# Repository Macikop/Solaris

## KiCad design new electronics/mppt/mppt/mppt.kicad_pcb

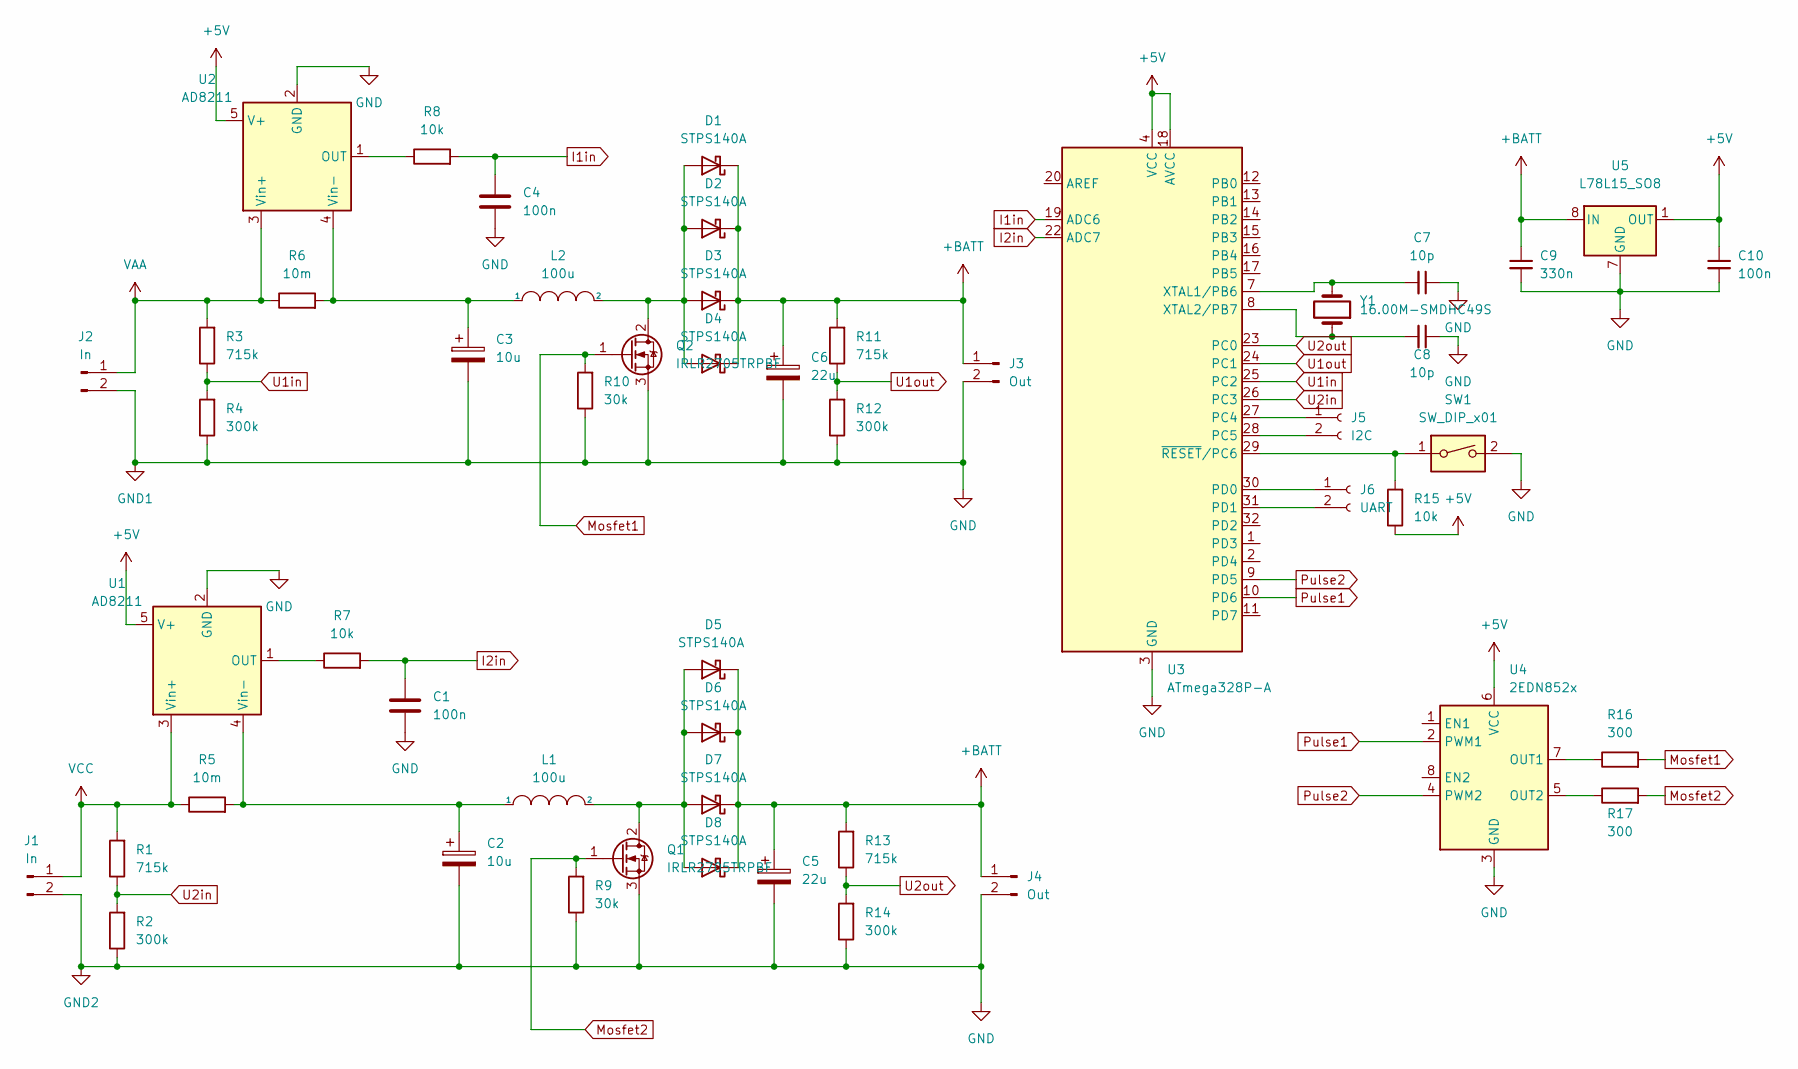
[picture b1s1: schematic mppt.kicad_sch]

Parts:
C1, C4, C10: 100n; R_1206_3216Metric_Pad1.30x1.75mm_HandSolder
C2, C3: 10u; CP_EIA-7343-15_Kemet-W_Pad2.25x2.55mm_HandSolder
C5, C6: 22u; CP_EIA-7343-15_Kemet-W_Pad2.25x2.55mm_HandSolder
C7, C8: 10p; R_1206_3216Metric_Pad1.30x1.75mm_HandSolder
C9: 330n; R_1206_3216Metric_Pad1.30x1.75mm_HandSolder
D1, D2, D3, D4, D5, D6, D7, D8: STPS140A; D_2010_5025Metric_Pad1.52x2.65mm_HandSolder
J1, J2: In; PowerPad
J3, J4: Out; PowerPad
J5: I2C; SolderWire-1.5sqmm_1x02_P7.8mm_D1.7mm_OD3.9mm
J6: UART; SolderWire-1.5sqmm_1x02_P7.8mm_D1.7mm_OD3.9mm
L1, L2: 100u; L_Bourns_SRR1208_12.7x12.7mm
Q1, Q2: IRLR2705TRPBF; TO-263-2
R1, R3, R11, R13: 715k; R_1206_3216Metric_Pad1.30x1.75mm_HandSolder
R2, R4, R12, R14: 300k; R_1206_3216Metric_Pad1.30x1.75mm_HandSolder
R5, R6: 10m; R_2010_5025Metric_Pad1.40x2.65mm_HandSolder
R7, R8, R15: 10k; R_1206_3216Metric_Pad1.30x1.75mm_HandSolder
R9, R10: 30k; R_1206_3216Metric_Pad1.30x1.75mm_HandSolder
R16, R17: 300; R_1206_3216Metric_Pad1.30x1.75mm_HandSolder
SW1: SW_DIP_x01; SolderJumper-2_P1.3mm_Open_RoundedPad1.0x1.5mm
U1, U2: AD8211; SOT-23-5
U3: ATmega328P-A; TQFP-32_7x7mm_P0.8mm
U4: 2EDN852x; SOIC-8_3.9x4.9mm_P1.27mm
U5: L78L15_SO8; SOIC-8_3.9x4.9mm_P1.27mm
Y1: 16.00M-SMDHC49S; Crystal_SMD_HC49-SD_HandSoldering

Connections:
+5V: C10.1, R15.1, U1.5 (V+), U2.5 (V+), U3.4 (VCC), U3.6 (VCC), U3.18 (AVCC), U4.6 (VCC), U5.1 (OUT)
+BATT: C5.1, C6.1, C9.1, D1.1 (K), D2.1 (K), D3.1 (K), D4.1 (K), D5.1 (K), D6.1 (K), D7.1 (K), D8.1 (K), J3.1, J4.1, R11.2, R13.2, U5.8 (IN)
GND: C1.2, C2.2, C3.2, C4.2, C5.2, C6.2, C7.1, C8.1, C9.2, C10.2, J1.2, J2.2, J3.2, J4.2, Q1.3 (S), Q2.3 (S), R2.1, R4.1, R9.1, R10.1, R12.1, R14.1, SW1.2, U1.2 (GND), U2.2 (GND), U3.3 (GND), U3.5 (GND), U3.21 (GND), U4.3 (GND), U5.2 (GND), U5.3 (GND), U5.6 (GND), U5.7 (GND)
I1in: C4.1, R8.2, U3.19 (ADC6)
I2in: C1.1, R7.2, U3.22 (ADC7)
Mosfet1: Q2.1 (G), R10.2, R16.2
Mosfet2: Q1.1 (G), R9.2, R17.2
unnamed: C2.1, L1.1, R5.2, U1.4 (Vin-)
unnamed: C3.1, L2.1, R6.2, U2.4 (Vin-)
unnamed: C7.2, U3.7 (XTAL1/PB6), Y1.2
unnamed: C8.2, U3.8 (XTAL2/PB7), Y1.1
unnamed: D1.2 (A), D2.2 (A), D3.2 (A), D4.2 (A), L2.2, Q2.2 (D)
unnamed: D5.2 (A), D6.2 (A), D7.2 (A), D8.2 (A), L1.2, Q1.2 (D)
unnamed: J5.1, U3.27 (PC4)
unnamed: J5.2, U3.28 (PC5)
unnamed: J6.1, U3.30 (PD0)
unnamed: J6.2, U3.31 (PD1)
unnamed: R7.1, U1.1 (OUT)
unnamed: R8.1, U2.1 (OUT)
unnamed: R15.2, SW1.1, U3.29 (~RESET/PC6)
unnamed: R16.1, U4.7 (OUT1)
unnamed: R17.1, U4.5 (OUT2)
Pulse1: U3.10 (PD6), U4.2 (PWM1)
Pulse2: U3.9 (PD5), U4.4 (PWM2)
U1in: R3.1, R4.2, U3.25 (PC2)
U1out: R11.1, R12.2, U3.24 (PC1)
U2in: R1.1, R2.2, U3.26 (PC3)
U2out: R13.1, R14.2, U3.23 (PC0)
VAA: J2.1, R3.2, R6.1, U2.3 (Vin+)
VCC: J1.1, R1.2, R5.1, U1.3 (Vin+)

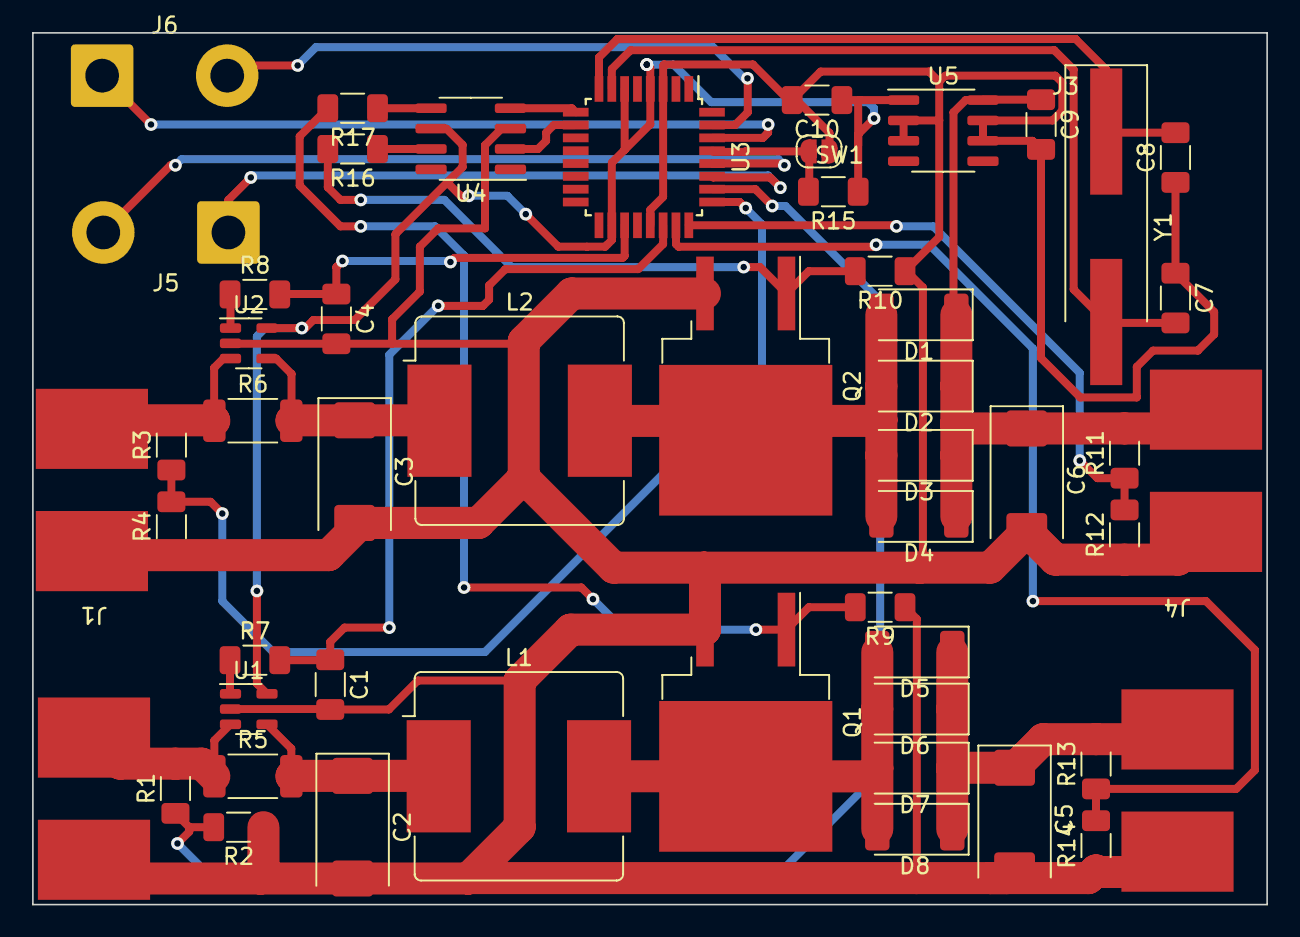
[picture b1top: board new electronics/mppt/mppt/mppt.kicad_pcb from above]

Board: 2 copper layers, 77.0 x 54.4 mm, 52 parts (0 on the bottom side), 30 nets.

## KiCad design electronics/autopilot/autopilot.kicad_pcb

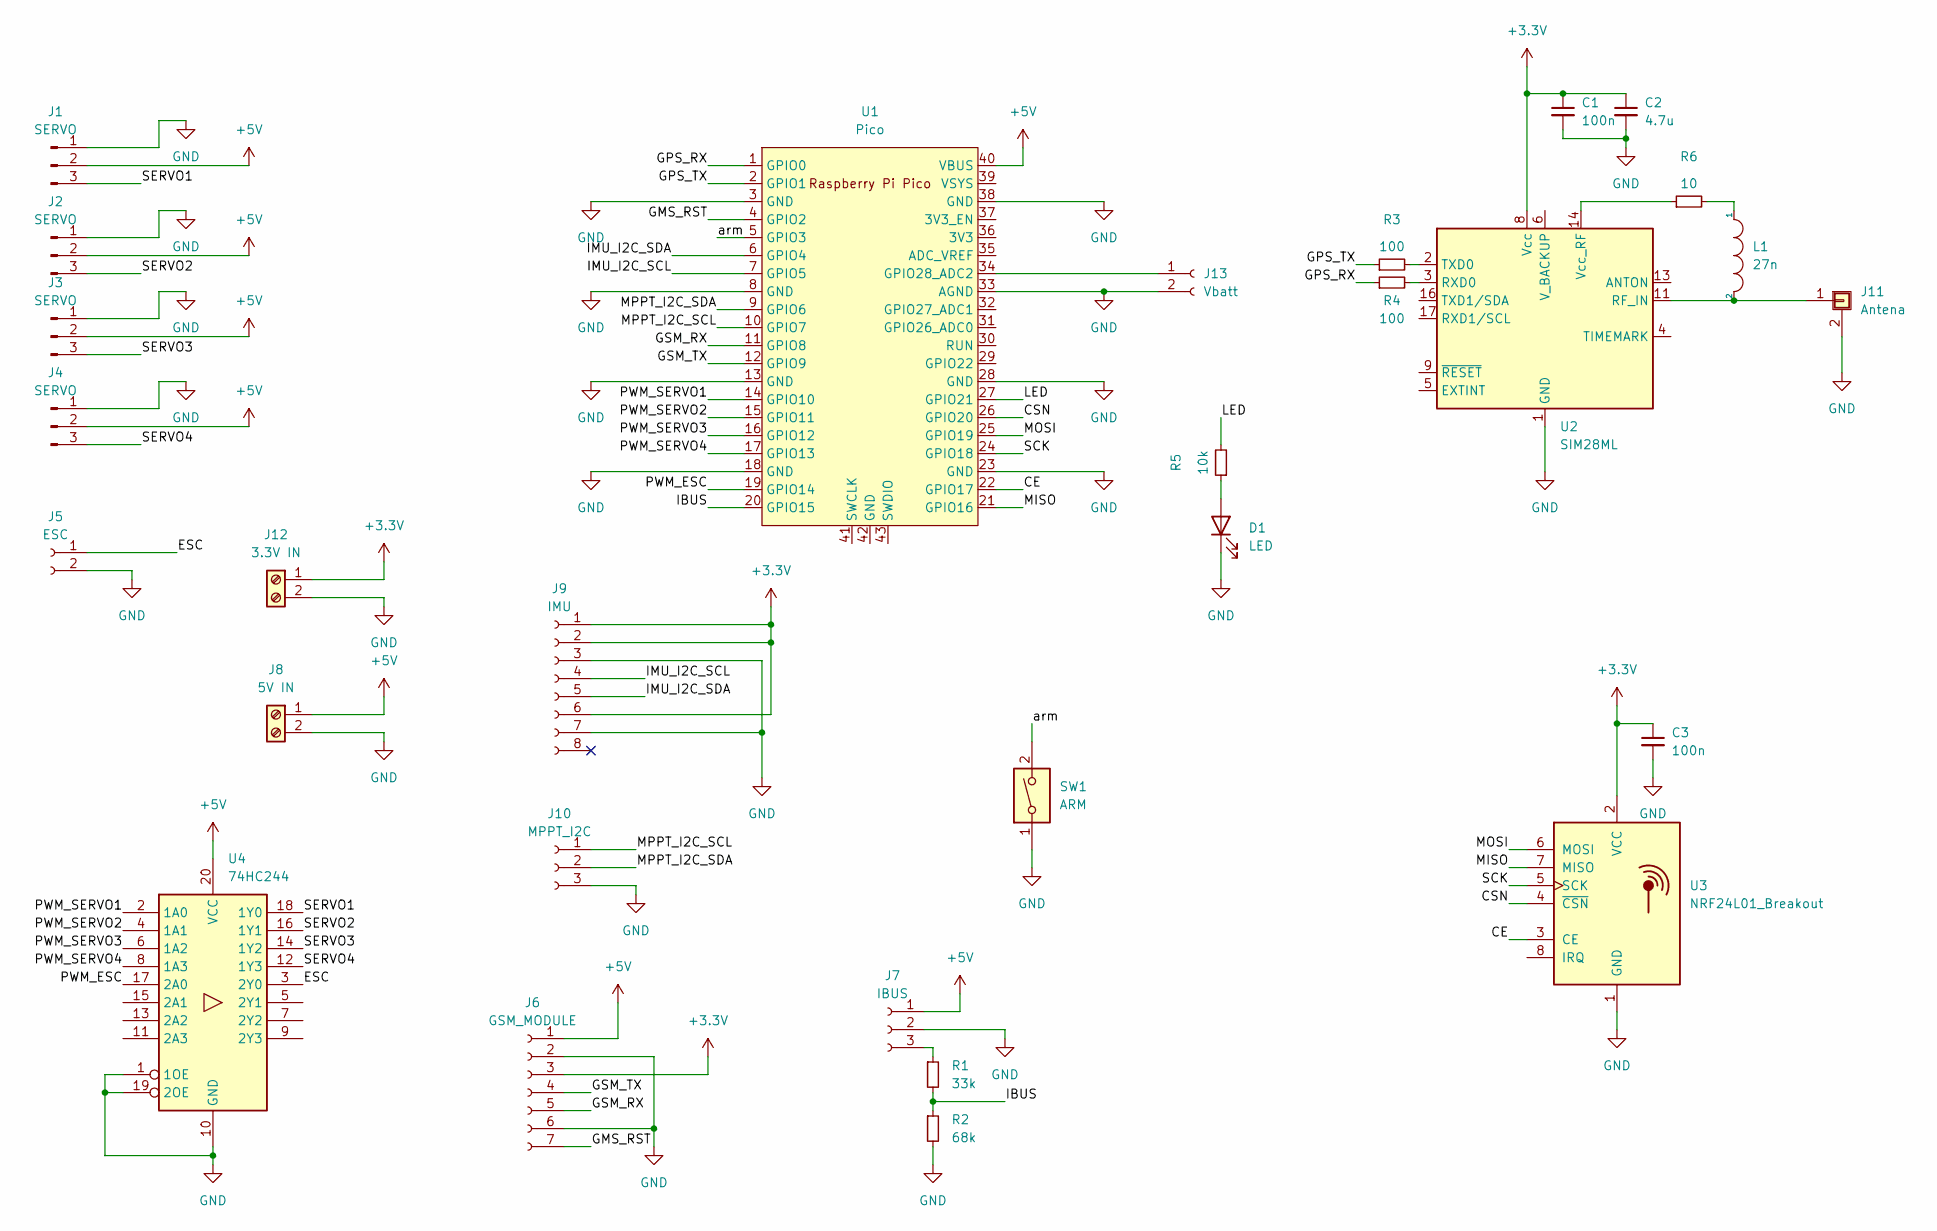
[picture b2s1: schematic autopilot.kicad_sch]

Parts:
C1, C3: 100n; C_1206_3216Metric_Pad1.33x1.80mm_HandSolder
C2: 4.7u; C_1206_3216Metric_Pad1.33x1.80mm_HandSolder
D1: LED; LED_1206_3216Metric_Pad1.42x1.75mm_HandSolder
J1, J2, J3, J4: SERVO; PinHeader_1x03_P2.54mm_Vertical
J5: ESC; PinHeader_1x02_P2.54mm_Vertical
J6: GSM_MODULE; PinHeader_1x07_P2.54mm_Vertical
J7: IBUS; PinHeader_1x03_P2.54mm_Vertical
J8: 5V IN; ARK
J9: IMU; PinHeader_1x08_P2.54mm_Vertical
J10: MPPT_I2C; PinHeader_1x03_P2.54mm_Vertical
J11: Antena; U.FL_Molex_MCRF_73412-0110_Vertical
J12: 3.3V IN; ARK
J13: Vbatt; PinHeader_1x02_P2.54mm_Vertical
L1: 27n; L_1210_3225Metric_Pad1.42x2.65mm_HandSolder
R1: 33k; R_1206_3216Metric_Pad1.30x1.75mm_HandSolder
R2: 68k; R_1206_3216Metric_Pad1.30x1.75mm_HandSolder
R3, R4: 100; R_1206_3216Metric_Pad1.30x1.75mm_HandSolder
R5: 10k; R_1206_3216Metric_Pad1.30x1.75mm_HandSolder
R6: 10; R_1206_3216Metric_Pad1.30x1.75mm_HandSolder
SW1: ARM; PinHeader_1x02_P2.54mm_Vertical
U1: Pico; RPi_Pico_SMD_TH
U2: SIM28ML
U3: NRF24L01_Breakout; nRF24L01_Breakout
U4: 74HC244; SO-20_12.8x7.5mm_P1.27mm

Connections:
+3.3V: C1.1, C2.1, C3.1, J6.3, J9.1, J9.2, J9.6, J12.1, U2.8 (Vcc), U3.2 (VCC)
+5V: J1.2, J2.2, J3.2, J4.2, J6.1, J7.1, J8.1, U1.40 (VBUS), U4.20 (VCC)
/CE: U1.22 (GPIO17), U3.3 (CE)
/CSN: U1.26 (GPIO20), U3.4 (~CSN)
/ESC: J5.1, U4.3 (2Y0)
/GMS_RST: J6.7, U1.4 (GPIO2)
/GPS_RX: R4.1, U1.1 (GPIO0)
/GPS_TX: R3.1, U1.2 (GPIO1)
/GSM_RX: J6.5, U1.11 (GPIO8)
/GSM_TX: J6.4, U1.12 (GPIO9)
/IBUS: R1.2, R2.1, U1.20 (GPIO15)
/IMU_I2C_SCL: J9.4, U1.7 (GPIO5)
/IMU_I2C_SDA: J9.5, U1.6 (GPIO4)
/LED: R5.2, U1.27 (GPIO21)
/MISO: U1.21 (GPIO16), U3.7 (MISO)
/MOSI: U1.25 (GPIO19), U3.6 (MOSI)
/MPPT_I2C_SCL: J10.1, U1.10 (GPIO7)
/MPPT_I2C_SDA: J10.2, U1.9 (GPIO6)
/PWM_ESC: U1.19 (GPIO14), U4.17 (2A0)
/PWM_SERVO1: U1.14 (GPIO10), U4.2 (1A0)
/PWM_SERVO2: U1.15 (GPIO11), U4.4 (1A1)
/PWM_SERVO3: U1.16 (GPIO12), U4.6 (1A2)
/PWM_SERVO4: U1.17 (GPIO13), U4.8 (1A3)
/SCK: U1.24 (GPIO18), U3.5 (SCK)
/SERVO1: J1.3, U4.18 (1Y0)
/SERVO2: J2.3, U4.16 (1Y1)
/SERVO3: J3.3, U4.14 (1Y2)
/SERVO4: J4.3, U4.12 (1Y3)
/arm: SW1.2, U1.5 (GPIO3)
GND: C1.2, C2.2, C3.2, D1.1 (K), J1.1, J2.1, J3.1, J4.1, J5.2, J6.2, J6.6, J7.2, J8.2, J9.3, J9.7, J10.3, J11.2 (Shield), J12.2, J13.2, R2.2, SW1.1, U1.3 (GND), U1.8 (GND), U1.13 (GND), U1.18 (GND), U1.23 (GND), U1.28 (GND), U1.33 (AGND), U1.38 (GND), U2.1 (GND), U2.10 (GND), U2.12 (GND), U3.1 (GND), U4.1 (1OE), U4.10 (GND), U4.19 (2OE)
unnamed: D1.2 (A), R5.1
unnamed: J7.3, R1.1
unnamed: J13.1, U1.34 (GPIO28_ADC2)
unnamed: L1.1, R6.2
unnamed: J11.1, L1.2, U2.11 (RF_IN)
unnamed: R3.2, U2.2 (TXD0)
unnamed: R4.2, U2.3 (RXD0)
unnamed: R6.1, U2.14 (Vcc_RF)

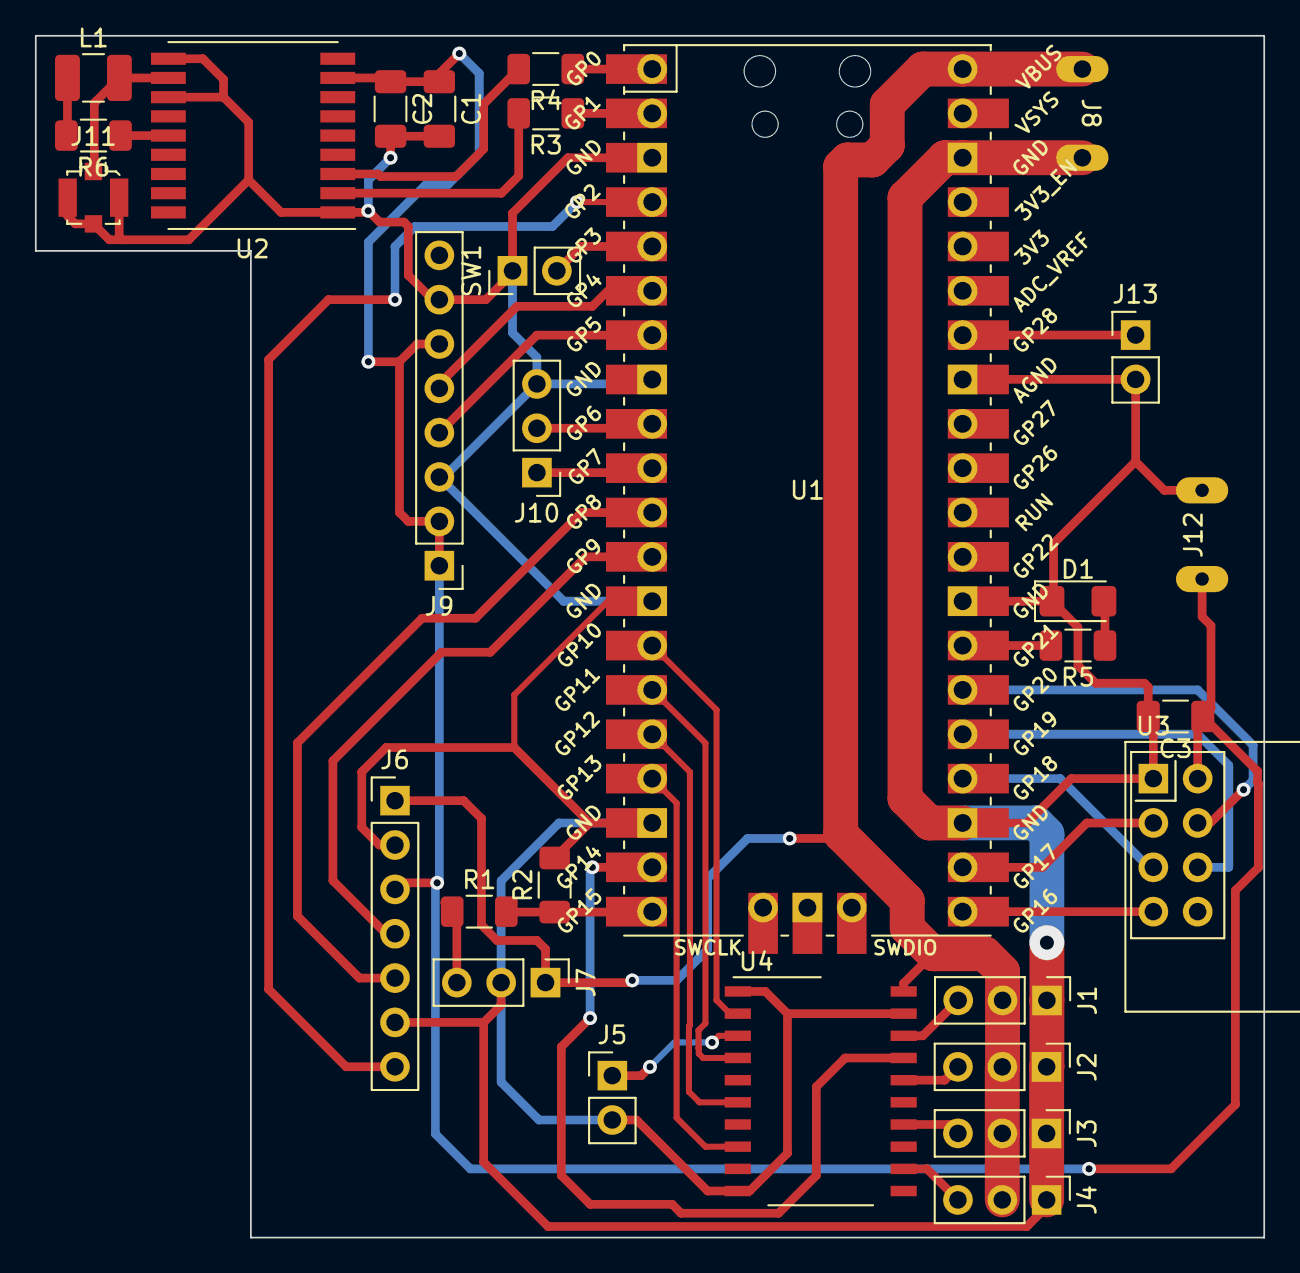
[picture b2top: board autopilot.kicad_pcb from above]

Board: 2 copper layers, 70.4 x 68.8 mm, 29 parts (0 on the bottom side), 38 nets.

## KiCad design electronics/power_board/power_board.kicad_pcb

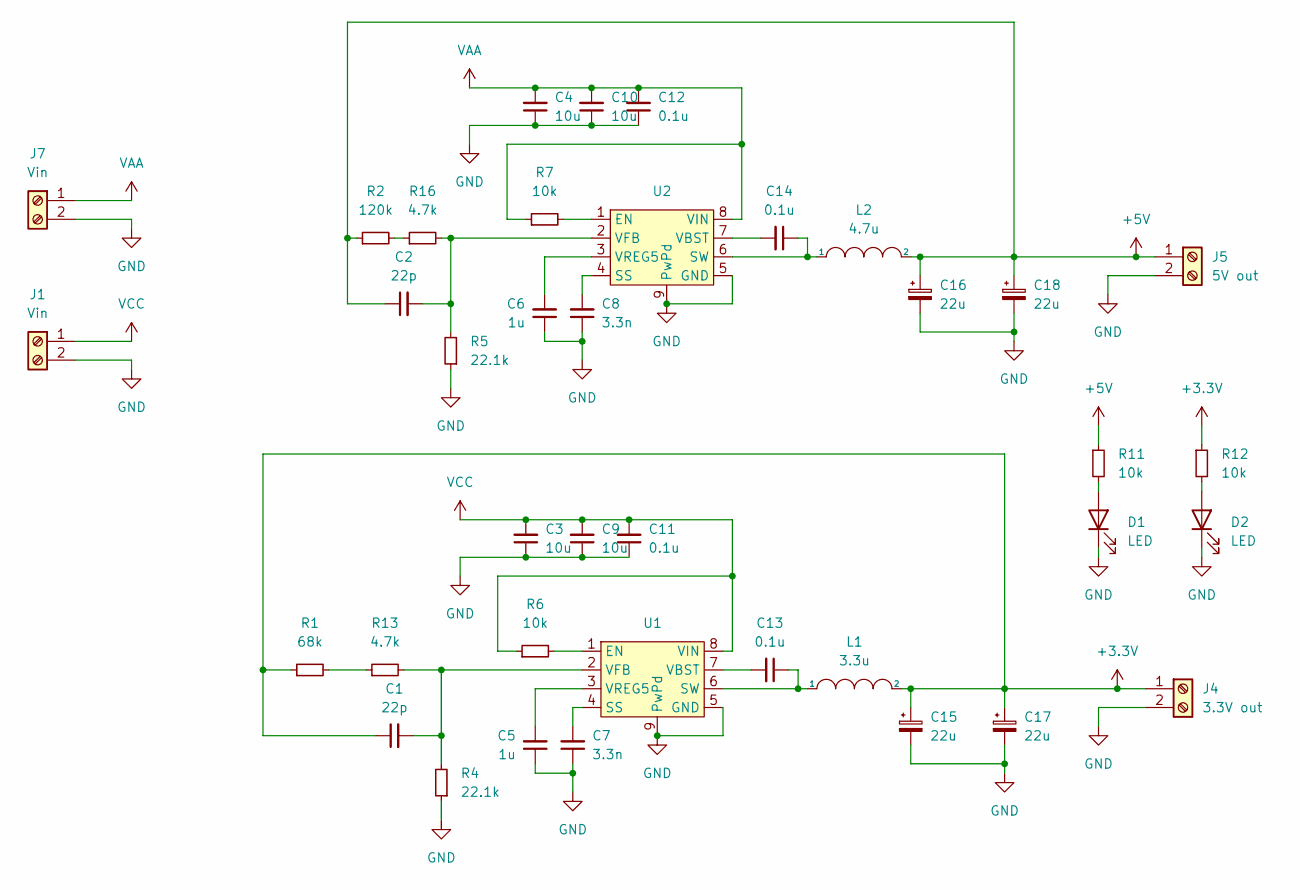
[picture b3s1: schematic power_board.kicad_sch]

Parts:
C1, C2: 22p; C_1206_3216Metric_Pad1.33x1.80mm_HandSolder
C3, C4, C9, C10: 10u; C_1206_3216Metric_Pad1.33x1.80mm_HandSolder
C5, C6: 1u; C_1206_3216Metric_Pad1.33x1.80mm_HandSolder
C7, C8: 3.3n; C_1206_3216Metric_Pad1.33x1.80mm_HandSolder
C11, C12, C13, C14: 0.1u; C_1206_3216Metric_Pad1.33x1.80mm_HandSolder
C15, C16, C17, C18: 22u; CP_Elec_6.3x5.4
D1, D2: LED; LED_1206_3216Metric_Pad1.42x1.75mm_HandSolder
J1, J7: Vin; ARK
J4: 3.3V out; ARK
J5: 5V out; ARK
L1: 3.3u; L_Neosid_SM-NE127_HandSoldering
L2: 4.7u; L_Neosid_SM-NE127_HandSoldering
R1: 68k; R_1206_3216Metric_Pad1.30x1.75mm_HandSolder
R2: 120k; R_1206_3216Metric_Pad1.30x1.75mm_HandSolder
R4, R5: 22.1k; R_1206_3216Metric_Pad1.30x1.75mm_HandSolder
R6, R7, R11, R12: 10k; R_1206_3216Metric_Pad1.30x1.75mm_HandSolder
R13, R16: 4.7k; R_1206_3216Metric_Pad1.30x1.75mm_HandSolder
U1, U2: TPS54228; HSOP-8-1EP_3.9x4.9mm_P1.27mm_EP2.41x3.1mm

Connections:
+3.3V: C1.1, C15.1, C17.1, J4.1, L1.2, R1.1, R12.1
+5V: C2.1, C16.1, C18.1, J5.1, L2.2, R2.1, R11.1
GND: C3.1, C4.1, C5.1, C6.1, C7.1, C8.1, C9.1, C10.1, C11.1, C12.1, C15.2, C16.2, C17.2, C18.2, D1.1 (K), D2.1 (K), J1.2, J4.2, J5.2, J7.2, R4.1, R5.1, U1.5 (GND), U1.9 (PwPd), U2.5 (GND), U2.9 (PwPd)
unnamed: C1.2, R4.2, R13.2, U1.2 (VFB)
unnamed: C2.2, R5.2, R16.2, U2.2 (VFB)
unnamed: C5.2, U1.3 (VREG5)
unnamed: C6.2, U2.3 (VREG5)
unnamed: C7.2, U1.4 (SS)
unnamed: C8.2, U2.4 (SS)
unnamed: C13.1, L1.1, U1.6 (SW)
unnamed: C13.2, U1.7 (VBST)
unnamed: C14.1, L2.1, U2.6 (SW)
unnamed: C14.2, U2.7 (VBST)
unnamed: D1.2 (A), R11.2
unnamed: D2.2 (A), R12.2
unnamed: R1.2, R13.1
unnamed: R2.2, R16.1
unnamed: R6.2, U1.1 (EN)
unnamed: R7.2, U2.1 (EN)
VAA: C4.2, C10.2, C12.2, J7.1, R7.1, U2.8 (VIN)
VCC: C3.2, C9.2, C11.2, J1.1, R6.1, U1.8 (VIN)

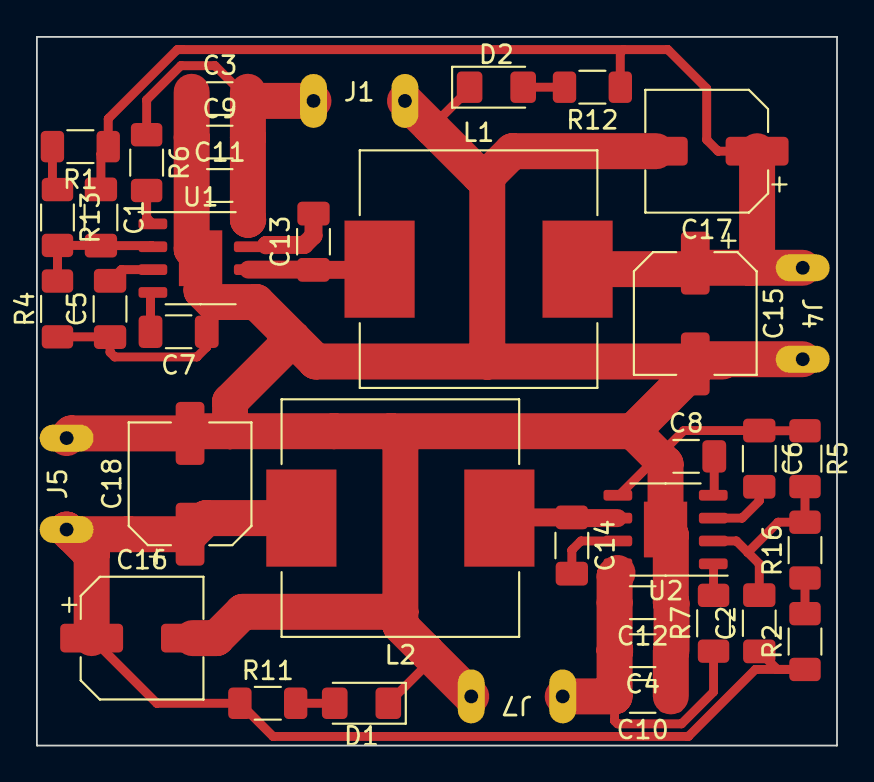
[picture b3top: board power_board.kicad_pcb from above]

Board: 2 copper layers, 44.5 x 39.4 mm, 38 parts (0 on the bottom side), 21 nets.

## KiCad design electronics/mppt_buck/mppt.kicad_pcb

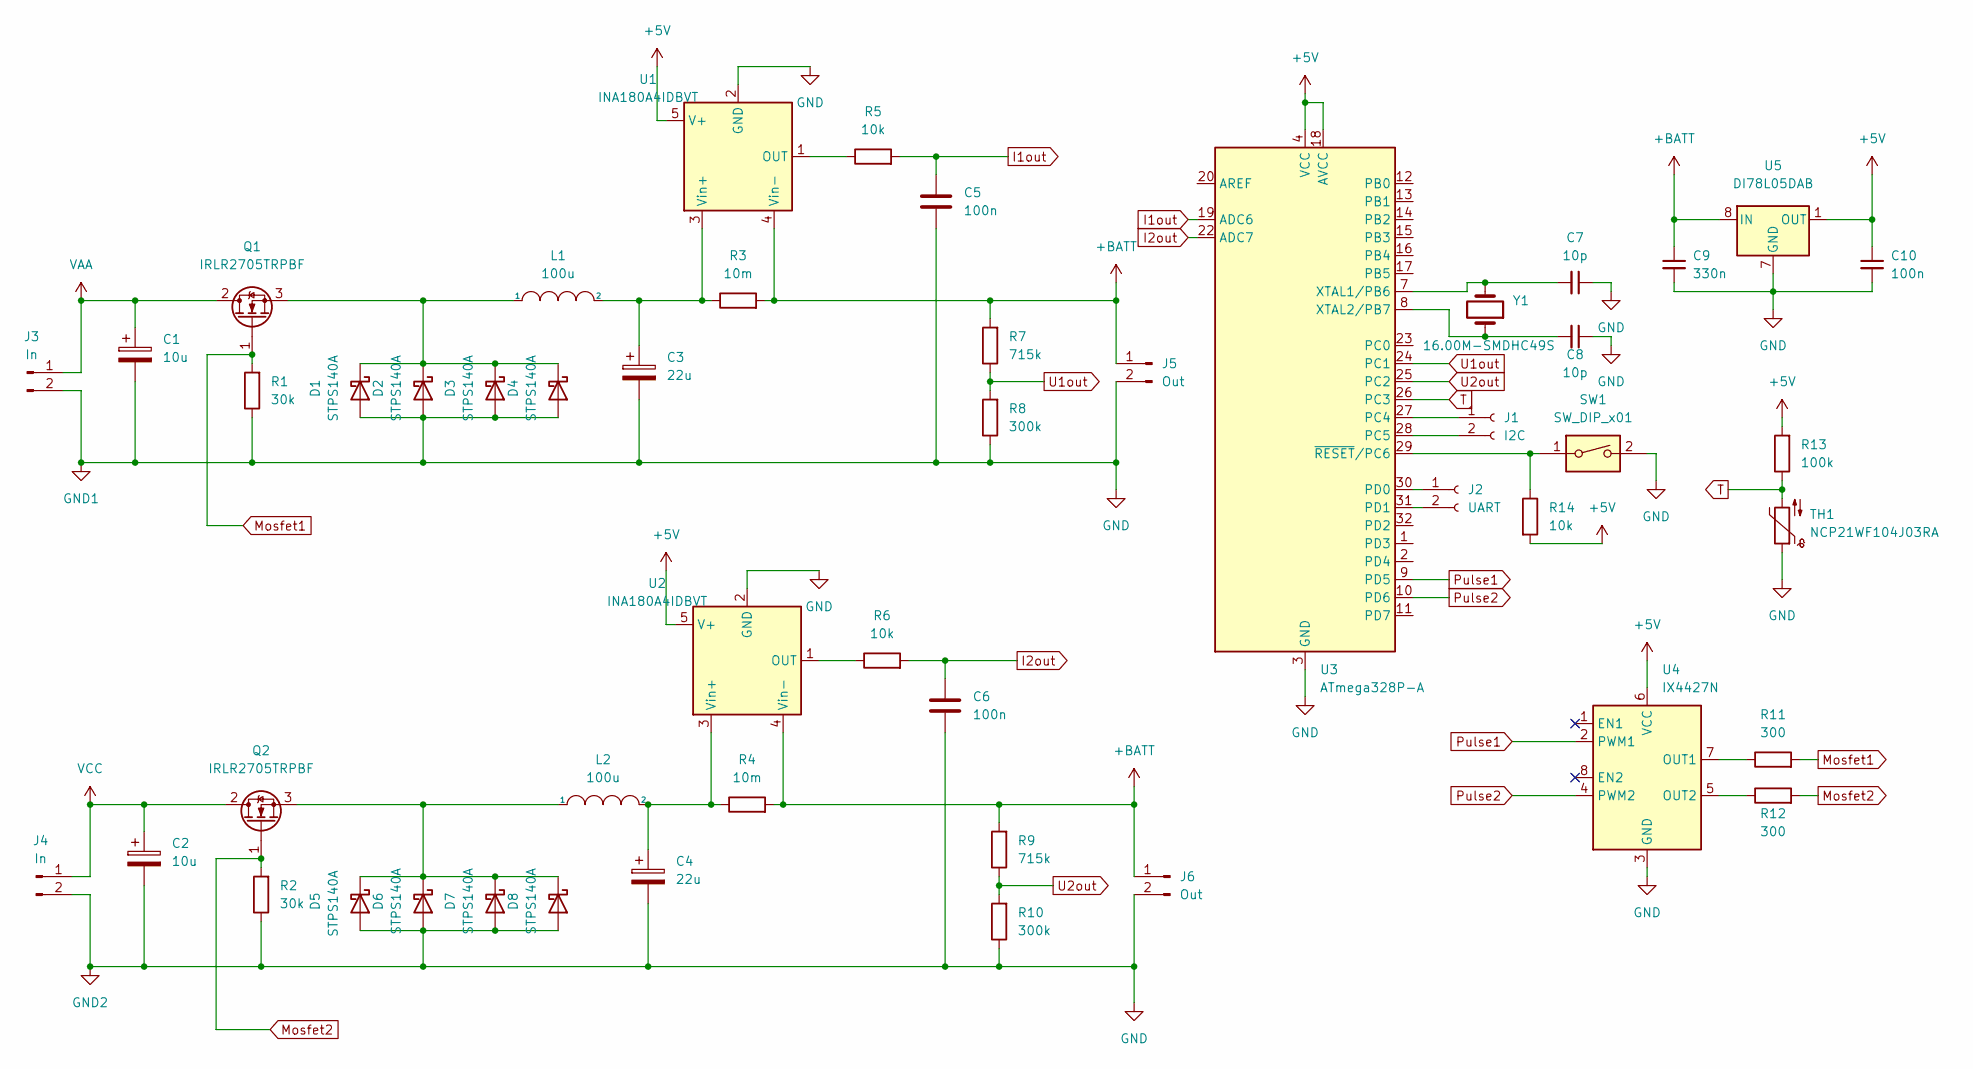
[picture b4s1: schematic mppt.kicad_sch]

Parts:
C1, C2: 10u; CP_Elec_5x5.4
C3, C4: 22u; CP_Elec_6.3x5.4
C5, C6, C10: 100n; R_1206_3216Metric_Pad1.30x1.75mm_HandSolder
C7, C8: 10p; R_1206_3216Metric_Pad1.30x1.75mm_HandSolder
C9: 330n; R_1206_3216Metric_Pad1.30x1.75mm_HandSolder
D1, D2, D3, D4, D5, D6, D7, D8: STPS140A; D_2010_5025Metric_Pad1.52x2.65mm_HandSolder
J1: I2C; SolderWire-1.5sqmm_1x02_P7.8mm_D1.7mm_OD3.9mm
J2: UART; SolderWire-1.5sqmm_1x02_P7.8mm_D1.7mm_OD3.9mm
J3, J4: In; PowerPad
J5, J6: Out; PowerPad
L1, L2: 100u; L_10.4x10.4_H4.8
Q1, Q2: IRLR2705TRPBF; TO-263-2
R1, R2: 30k; R_1206_3216Metric_Pad1.30x1.75mm_HandSolder
R3, R4: 10m; R_2010_5025Metric_Pad1.40x2.65mm_HandSolder
R5, R6, R14: 10k; R_1206_3216Metric_Pad1.30x1.75mm_HandSolder
R7, R9: 715k; R_1206_3216Metric_Pad1.30x1.75mm_HandSolder
R8, R10: 300k; R_1206_3216Metric_Pad1.30x1.75mm_HandSolder
R11, R12: 300; R_1206_3216Metric_Pad1.30x1.75mm_HandSolder
R13: 100k; R_1206_3216Metric_Pad1.30x1.75mm_HandSolder
SW1: SW_DIP_x01; SolderJumper-2_P1.3mm_Open_RoundedPad1.0x1.5mm
TH1: NCP21WF104J03RA; R_0805_2012Metric
U1, U2: INA180A4IDBVT; SOT-23-5
U3: ATmega328P-A; TQFP-32_7x7mm_P0.8mm
U4: IX4427N; SOIC-8_3.9x4.9mm_P1.27mm
U5: DI78L05DAB; SOIC-8_3.9x4.9mm_P1.27mm
Y1: 16.00M-SMDHC49S; Crystal_SMD_HC49-SD_HandSoldering

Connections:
+5V: C10.1, R13.2, R14.2, U1.5 (V+), U2.5 (V+), U3.4 (VCC), U3.6 (VCC), U3.18 (AVCC), U4.6 (VCC), U5.1 (OUT)
+BATT: C9.1, J5.1, J6.1, R3.2, R4.2, R7.2, R9.2, U1.4 (Vin-), U2.4 (Vin-), U5.8 (IN)
GND: C1.2, C2.2, C3.2, C4.2, C5.2, C6.2, C7.1, C8.1, C9.2, C10.2, D1.2 (A), D2.2 (A), D3.2 (A), D4.2 (A), D5.2 (A), D6.2 (A), D7.2 (A), D8.2 (A), J3.2, J4.2, J5.2, J6.2, R1.1, R2.1, R8.1, R10.1, SW1.2, TH1.1, U1.2 (GND), U2.2 (GND), U3.3 (GND), U3.5 (GND), U3.21 (GND), U4.3 (GND), U5.2 (GND), U5.3 (GND), U5.6 (GND), U5.7 (GND)
I1out: C5.1, R5.2, U3.19 (ADC6)
I2out: C6.1, R6.2, U3.22 (ADC7)
Mosfet1: Q1.1 (G), R1.2, R11.2
Mosfet2: Q2.1 (G), R2.2, R12.2
unnamed: C3.1, L1.2, R3.1, U1.3 (Vin+)
unnamed: C4.1, L2.2, R4.1, U2.3 (Vin+)
unnamed: C7.2, U3.7 (XTAL1/PB6), Y1.2
unnamed: C8.2, U3.8 (XTAL2/PB7), Y1.1
unnamed: D1.1 (K), D2.1 (K), D3.1 (K), D4.1 (K), L1.1, Q1.3 (S)
unnamed: D5.1 (K), D6.1 (K), D7.1 (K), D8.1 (K), L2.1, Q2.3 (S)
unnamed: J1.1, U3.27 (PC4)
unnamed: J1.2, U3.28 (PC5)
unnamed: J2.1, U3.30 (PD0)
unnamed: J2.2, U3.31 (PD1)
unnamed: R5.1, U1.1 (OUT)
unnamed: R6.1, U2.1 (OUT)
unnamed: R11.1, U4.7 (OUT1)
unnamed: R12.1, U4.5 (OUT2)
unnamed: R14.1, SW1.1, U3.29 (~RESET/PC6)
Pulse1: U3.9 (PD5), U4.2 (PWM1)
Pulse2: U3.10 (PD6), U4.4 (PWM2)
T: R13.1, TH1.2, U3.26 (PC3)
U1out: R7.1, R8.2, U3.24 (PC1)
U2out: R9.1, R10.2, U3.25 (PC2)
VAA: C1.1, J3.1, Q1.2 (D)
VCC: C2.1, J4.1, Q2.2 (D)

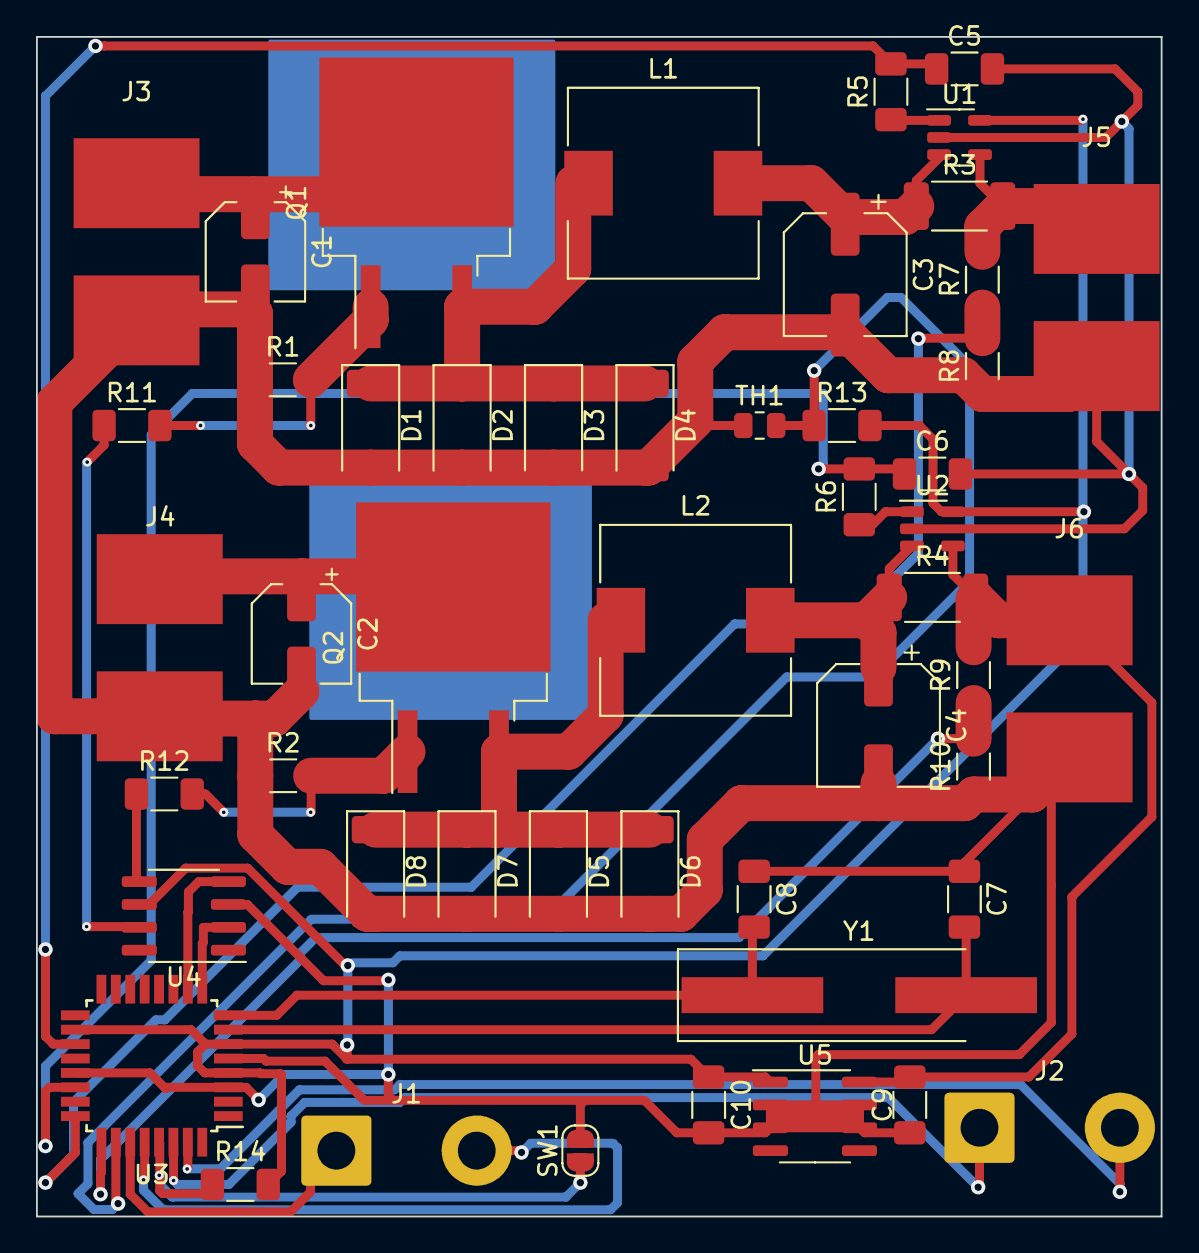
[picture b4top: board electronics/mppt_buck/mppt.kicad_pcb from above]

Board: 2 copper layers, 62.5 x 65.5 mm, 50 parts (0 on the bottom side), 29 nets.

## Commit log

2022-11-11 first version of mppt
2022-11-12 buck mppt added
2022-11-15 added links to resistors
2022-11-15 autopilot board almost finished
2022-11-17 autopilot schematic first version
2022-11-19 autopilot board finished
2022-11-20 minor fixes
2022-11-20 Added Żebros to model
2022-11-21 Added Inventor Assembly file
2022-11-21 autopilot finished secend version
2022-11-21 mppt cpu reset fix
2022-11-22 Added pianka to skrzydlo, and cleaned up parts
2022-11-22 power board schematic almost finished
2022-11-25 power board pcb not finished
2022-11-25 shop links added
2022-11-25 links fixed
2022-11-25 futher fixes
2022-11-25 powerboard link fix
2022-11-25 links almost fixed finally
2022-11-28 mppt part list corrected
2022-12-02 power board finished
2022-12-03 autopilot board minor fixes
2022-12-07 wing joint added
2022-12-09 Addec second wing assembly
2022-12-09 kadlub added
2022-12-09 kadlub nose need fix
2022-12-09 Changed Kadlub nose to be more boar-like
2022-12-12 secend version of kadlub
2022-12-16 added mewa.iam and added dimensions to zebro_kadlub.ipt
2022-12-27 new model
2022-12-29 tail ribs
2023-01-04 new kuplung and other
2023-01-05 added samolot assembly
2023-01-05 fixed samolot
2023-01-15 new kadłub
2023-01-16 Fixed main assembly
2023-02-05 added wingspar brackets
2023-02-07 3d renders of electronics
2023-02-08 fixed tail angle, set appearance on all parts
2023-02-10 added poszycie, silnik, panele and added colours to model
2023-02-10 added samolot bez sparow
2023-02-14 added stls
2023-02-21 renders, pdf and merge
2023-02-21 autopilot schematic fixed
2023-03-20 added connector to nowy kadlub
2023-03-20 autopilot not yest
2023-03-21 minor changes
2023-03-21 cleaned things up
2023-03-21 cleaned thing up
2023-04-06 added milling jigsaw
2023-04-15 fixed kadlub.ipt
2023-04-19 electronics remake
2023-04-19 autopilot rework
2023-04-30 added frez_zebra
2023-05-07 added jig
2023-05-08 updated jig
2023-05-09 added back jig
2023-05-20 added servo slot in tail
2023-05-21 added presentation
2023-06-08 added servo slots to kupplung
2023-08-17 autopilot buffer footprint fixed
2023-09-12 small fixes
2023-10-06 new mppt design
